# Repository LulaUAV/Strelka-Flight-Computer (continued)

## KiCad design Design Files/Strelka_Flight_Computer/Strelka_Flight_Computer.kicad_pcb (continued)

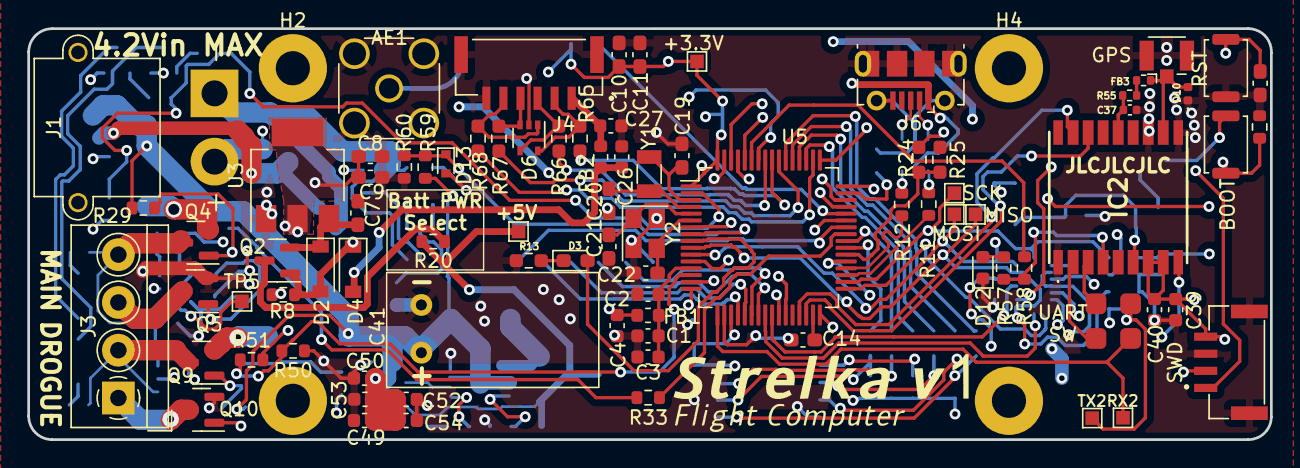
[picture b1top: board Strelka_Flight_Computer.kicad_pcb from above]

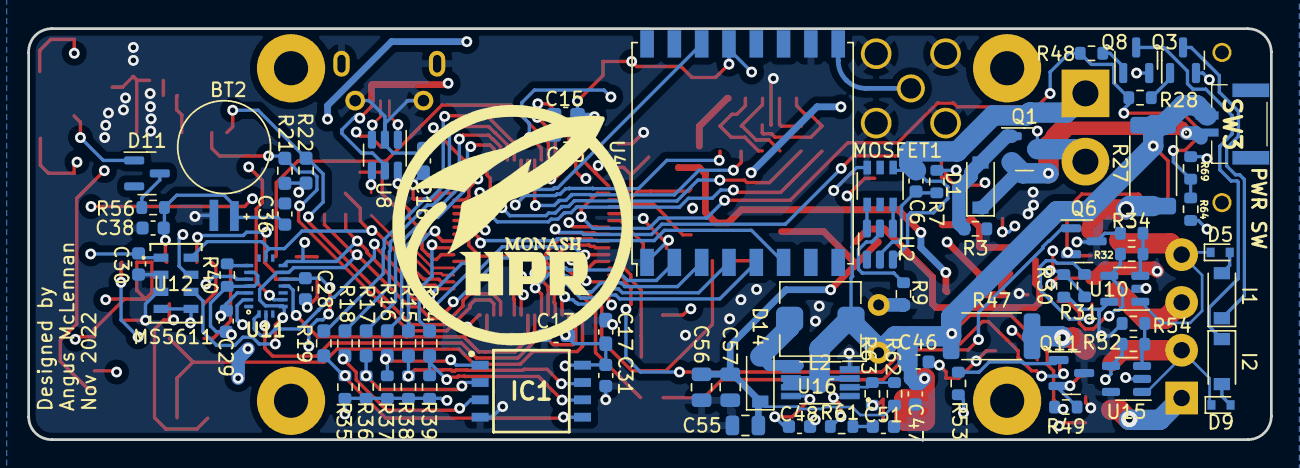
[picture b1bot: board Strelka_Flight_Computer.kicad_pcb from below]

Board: 4 copper layers, 91.0 x 30.1 mm, 168 parts (79 on the bottom side), 123 nets.

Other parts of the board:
D5: 1SS388; D_SOD-523
I1: AL5809-30S1-7; D_SOD-123
Q3, Q4: AO3401A; SOT-23
Q5: AP2300; SOT-23
Q6: MMBT2222; SOT-23
R27: 2R; R_2512_6332Metric
R28, R31, R33, R34: 1k; R_0603_1608Metric
R29, R30, R32, R64: 100k; R_0603_1608Metric
TP5: TestPoint; TestPoint_Pad_1.0x1.0mm
U10: LM321; SOT-23-5

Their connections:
+3V3: Q3.2 (S), R64.2, U10.2 (V-); also elsewhere on the board
/Actuators/CONT_TEST_EN: R28.2, R64.1; also elsewhere on the board
/Actuators/DROGUE_CONT: R32.1, TP5.1, U10.4; also elsewhere on the board
/Actuators/DROGUE_H: R33.2; also elsewhere on the board
/Actuators/DROGUE_L: R30.2, R31.1; also elsewhere on the board
/Actuators/Ematch_Drogue1/EMATCH+: D5.1 (K), Q4.3 (D), U10.1 (+); also elsewhere on the board
/Actuators/Ematch_Drogue1/EMATCH-: Q5.3 (D); also elsewhere on the board
GND: Q5.2 (S), Q6.3 (E), R30.1, R34.1, U10.5 (V+); also elsewhere on the board
unnamed: D5.2 (A), I1.2
unnamed: I1.1, Q3.3 (D)
unnamed: Q3.1 (G), R28.1
unnamed: Q4.1 (G), Q6.2 (C), R29.1
unnamed: Q4.2 (S), R27.2
unnamed: Q5.1 (G), R31.2
unnamed: Q6.1 (B), R33.1
unnamed: R32.2, R34.2, U10.3 (-)
VDC: R27.1, R29.2; also elsewhere on the board

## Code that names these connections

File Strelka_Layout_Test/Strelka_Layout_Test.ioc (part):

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Mcu.Name=STM32F405RGTx
Mcu.Package=LQFP64
Mcu.UserName=STM32F405RGTx
PA0-WKUP.GPIOParameters=GPIO_Label
PA0-WKUP.GPIO_Label=MAIN_L
PA0-WKUP.Signal=GPIO_Output
PA1.GPIOParameters=GPIO_Label
PA1.GPIO_Label=MAIN_H
PA1.Signal=GPIO_Output
PA10.Mode=Asynchronous
PA10.Signal=USART1_RX
PA11.GPIOParameters=GPIO_Label
PA11.GPIO_Label=IO_RF
PA11.Signal=GPXTI11
PA12.GPIOParameters=GPIO_Label
PA12.GPIO_Label=GYRO_CS
PA12.Signal=GPIO_Output
PA13.Mode=Serial_Wire
PA13.Signal=SYS_JTMS-SWDIO
PA14.Mode=Serial_Wire
PA14.Signal=SYS_JTCK-SWCLK
PA15.Mode=NSS_Signal_Hard_Output
PA15.Signal=SPI3_NSS
PA2.Mode=Asynchronous
PA2.Signal=USART2_TX
PA3.Mode=Asynchronous
PA3.Signal=USART2_RX
PA4.Mode=NSS_Signal_Hard_Output
PA4.Signal=SPI1_NSS
PA5.Mode=Full_Duplex_Master
PA5.Signal=SPI1_SCK
PA6.Mode=Full_Duplex_Master
PA6.Signal=SPI1_MISO
PA7.Mode=Full_Duplex_Master
PA7.Signal=SPI1_MOSI
PA8.GPIOParameters=GPIO_Label
PA8.GPIO_Label=DROGUE_H
PA8.Signal=GPIO_Output
PA9.Mode=Asynchronous
PA9.Signal=USART1_TX
PB0.GPIOParameters=GPIO_Label
PB0.GPIO_Label=DROGUE_CONT
PB0.Signal=ADCx_IN8
PB1.GPIOParameters=GPIO_Label
PB1.GPIO_Label=MAIN_CONT
PB1.Signal=ADCx_IN9
PB10.Mode=I2C
PB10.Signal=I2C2_SCL
PB11.Mode=I2C
PB11.Signal=I2C2_SDA
PB12.GPIOParameters=GPIO_Label
PB12.GPIO_Label=MAG_CS
PB12.Signal=GPIO_Output
PB13.Mode=Full_Duplex_Master
PB13.Signal=SPI2_SCK
PB14.Mode=Device_Only_FS
PB14.Signal=USB_OTG_HS_DM
PB15.Mode=Device_Only_FS
PB15.Signal=USB_OTG_HS_DP
PB3.Mode=Full_Duplex_Master
PB3.Signal=SPI3_SCK
PB4.Mode=Full_Duplex_Master
PB4.Signal=SPI3_MISO
PB5.Mode=Full_Duplex_Master
PB5.Signal=SPI3_MOSI
PB6.GPIOParameters=GPIO_Label
PB6.GPIO_Label=DROGUE_L
PB6.Signal=GPIO_Output
PB7.GPIOParameters=GPIO_Label
PB7.GPIO_Label=GPS_PPS
PB7.Signal=GPXTI7
PB8.GPIOParameters=GPIO_Label
PB8.GPIO_Label=BARO_CS
PB8.Signal=GPIO_Output
PB9.GPIOParameters=GPIO_Label
PB9.GPIO_Label=ACCEL_CS
PB9.Signal=GPIO_Output
PC0.GPIOParameters=GPIO_Label
PC0.GPIO_Label=BATT_VOLT_READ
PC0.Signal=ADCx_IN10
PC1.GPIOParameters=GPIO_Label
PC1.GPIO_Label=LED_INDICATOR
PC1.Signal=GPIO_Output
PC10.Mode=SD_4_bits_Wide_bus
PC10.Signal=SDIO_D2
PC11.Mode=SD_4_bits_Wide_bus
PC11.Signal=SDIO_D3
PC12.Mode=SD_4_bits_Wide_bus
PC12.Signal=SDIO_CK
PC13-ANTI_TAMP.GPIOParameters=GPIO_Label
PC13-ANTI_TAMP.GPIO_Label=CONT_TEST_EN
PC13-ANTI_TAMP.Signal=GPIO_Output
PC14-OSC32_IN.Mode=LSE-External-Oscillator
PC14-OSC32_IN.Signal=RCC_OSC32_IN
PC15-OSC32_OUT.Mode=LSE-External-Oscillator
PC15-OSC32_OUT.Signal=RCC_OSC32_OUT
PC2.Mode=Full_Duplex_Master
PC2.Signal=SPI2_MISO
PC3.Mode=Full_Duplex_Master
PC3.Signal=SPI2_MOSI
PC4.GPIOParameters=GPIO_Label
PC4.GPIO_Label=ACCEL_INT
PC4.Signal=GPXTI4
PC5.GPIOParameters=GPIO_Label
PC5.GPIO_Label=GYRO_INT
PC5.Signal=GPXTI5
PC6.GPIOParameters=GPIO_Label
PC6.GPIO_Label=MAG_INT
PC6.Signal=GPXTI6
PC7.GPIOParameters=GPIO_Label
PC7.GPIO_Label=SD_DET
PC7.Signal=GPIO_Input
PC8.Mode=SD_4_bits_Wide_bus
PC8.Signal=SDIO_D0
PC9.Mode=SD_4_bits_Wide_bus
PC9.Signal=SDIO_D1
PD2.Mode=SD_4_bits_Wide_bus
PD2.Signal=SDIO_CMD
PH0-OSC_IN.Mode=HSE-External-Oscillator
PH0-OSC_IN.Signal=RCC_OSC_IN
PH1-OSC_OUT.Mode=HSE-External-Oscillator
PH1-OSC_OUT.Signal=RCC_OSC_OUT
RCC.HSE_VALUE=24000000
RCC.SYSCLKFreq_VALUE=168000000
RCC.SYSCLKSource=RCC_SYSCLKSOURCE_PLLCLK
board=custom

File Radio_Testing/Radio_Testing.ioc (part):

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Mcu.Name=STM32F405RGTx
Mcu.Package=LQFP64
Mcu.UserName=STM32F405RGTx
PA0-WKUP.Mode=CTS_RTS
PA0-WKUP.Signal=USART2_CTS
PA1.Mode=CTS_RTS
PA1.Signal=USART2_RTS
PA10.Mode=Asynchronous
PA10.Signal=USART1_RX
PA11.Signal=USART1_CTS
PA12.Signal=USART1_RTS
PA13.Signal=SYS_JTMS-SWDIO
PA14.Signal=SYS_JTCK-SWCLK
PA2.Mode=Asynchronous
PA2.Signal=USART2_TX
PA3.Mode=Asynchronous
PA3.Signal=USART2_RX
PA4.GPIOParameters=GPIO_Label
PA4.GPIO_Label=RF_SPI_NSS
PA4.Signal=GPIO_Output
PA5.Mode=Full_Duplex_Master
PA5.Signal=SPI1_SCK
PA6.Mode=Full_Duplex_Master
PA6.Signal=SPI1_MISO
PA7.Mode=Full_Duplex_Master
PA7.Signal=SPI1_MOSI
PA8.GPIOParameters=GPIO_Label
PA8.GPIO_Label=IO5_RF
PA8.Signal=GPXTI8
PA9.Mode=Asynchronous
PA9.Signal=USART1_TX
PB0.GPIOParameters=GPIO_Label
PB0.GPIO_Label=RESET_RF
PB0.Signal=GPIO_Output
PB1.GPIOParameters=GPIO_Label
PB1.GPIO_Label=IO0_RF
PB1.Signal=GPXTI1
PB10.GPIOParameters=GPIO_Label
PB10.GPIO_Label=IO1_RF
PB10.Signal=GPXTI10
PB11.GPIOParameters=GPIO_Label
PB11.GPIO_Label=IO2_RF
PB11.Signal=GPXTI11
PB12.GPIOParameters=GPIO_Label
PB12.GPIO_Label=IO3_RF
PB12.Signal=GPXTI12
PB13.GPIOParameters=GPIO_Label
PB13.GPIO_Label=IO4_RF
PB13.Signal=GPXTI13
PB14.Mode=Device_Only_FS
PB14.Signal=USB_OTG_HS_DM
PB15.Mode=Device_Only_FS
PB15.Signal=USB_OTG_HS_DP
PC14-OSC32_IN.Mode=LSE-External-Oscillator
PC14-OSC32_IN.Signal=RCC_OSC32_IN
PC15-OSC32_OUT.Mode=LSE-External-Oscillator
PC15-OSC32_OUT.Signal=RCC_OSC32_OUT
PD2.GPIOParameters=GPIO_Label
PD2.GPIO_Label=INDICATOR_LED
PD2.Signal=GPIO_Output
PH0-OSC_IN.Mode=HSE-External-Oscillator
PH0-OSC_IN.Signal=RCC_OSC_IN
PH1-OSC_OUT.Mode=HSE-External-Oscillator
PH1-OSC_OUT.Signal=RCC_OSC_OUT
RCC.HSE_VALUE=24000000
RCC.SYSCLKFreq_VALUE=168000000
RCC.SYSCLKSource=RCC_SYSCLKSOURCE_PLLCLK
board=custom

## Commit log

2022-09-22 Added features.xlsx
2022-09-22 Added features.xls
2022-09-22 Added boost converter
2022-09-28 Added sensors
2022-09-29 Added BMX055
2022-10-04 Working SPICE sim for ematch continuity circuit
2022-10-23 Added power board, almost finished Strelka schematic
2022-10-24 Pin mapping and created STM32 .ioc for reference
2022-10-24 Added to continuity circuit
2022-10-24 Added new UBLOX GPS
2022-10-27 Added motor driver to power board
2022-11-02 Switched order of pull-down resistor into ematch mostfet sw
2022-11-02 Changed boost converter
2022-11-02 Deleted extra boost circuit and L80 schematic
2022-11-02 Started writing libraries for board functions
2022-11-02 Started draft of Software ICD
2022-11-02 Ported project to updated CUBE IDE
2022-11-03 Finished continuity and deployment class
2022-11-03 Started creating relevent header files
2022-11-06 Added working SPI comms test
2022-11-07 Added radio testing
2022-11-07 Started component placement
2022-11-08 Rad testing updates
2022-11-09 First go at routing
2022-11-10 Power routing finished
2022-11-12 Creating BOM
2022-11-12 redo placement
2022-11-13 Setting up gs code
2022-11-13 PCB ordered
2022-11-13 Started ground station python
2022-11-19 Added firmware drivers - untested
2022-11-26 Added some changes
